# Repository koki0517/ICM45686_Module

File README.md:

# ICM45686_Module

ICM-45686 センサーモジュールのKiCad設計データです。

他の基板に実装するための[シンボル・フットプリント・3Dライブラリ](library/README.md)を用意しています。母基板側のピンソケットとICM基板側のピンヘッダーを接続した構成を、1つのフットプリントと3Dモデルで表しています。

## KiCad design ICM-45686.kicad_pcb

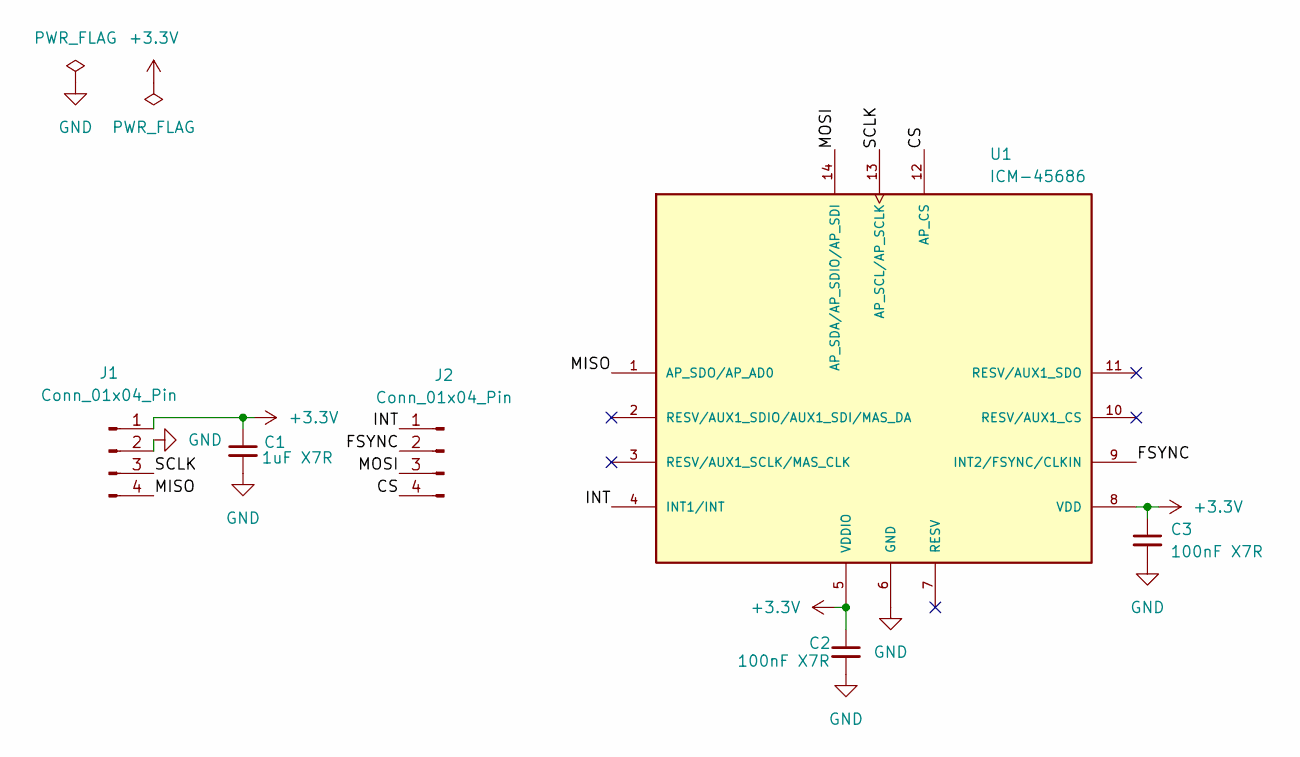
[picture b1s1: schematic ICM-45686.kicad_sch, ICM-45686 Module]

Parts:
C1: 1uF X7R; C_0402_1005Metric; LCSC C52923
C2, C3: 100nF X7R; C_0402_1005Metric; LCSC C1525
J1, J2: Conn_01x04_Pin; PinHeader_1x04_P2.54mm_Vertical
U1: ICM-45686; IC_ICM-45686; PARTREV 0.2; LCSC C22459454

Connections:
+3.3V: C1.1, C2.1, C3.1, J1.1, U1.5 (VDDIO), U1.8 (VDD)
/CS: J2.4, U1.12 (AP_CS)
/FSYNC: J2.2, U1.9 (INT2/FSYNC/CLKIN)
/INT: J2.1, U1.4 (INT1/INT)
/MISO: J1.4, U1.1 (AP_SDO/AP_AD0)
/MOSI: J2.3, U1.14 (AP_SDA/AP_SDIO/AP_SDI)
/SCLK: J1.3, U1.13 (AP_SCL/AP_SCLK)
GND: C1.2, C2.2, C3.2, J1.2, U1.6 (GND)

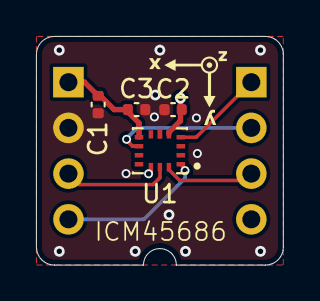
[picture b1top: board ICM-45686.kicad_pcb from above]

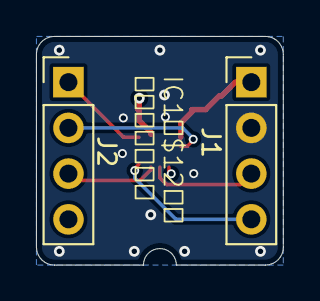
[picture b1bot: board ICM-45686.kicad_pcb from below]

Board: 4 copper layers, 13.7 x 12.7 mm, 6 parts (2 on the bottom side), 8 nets.
